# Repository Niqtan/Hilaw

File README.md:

# Hilaw (3D Printed Instant Camera)

## Project Aims

Hilaw, in english, Raw, is a hybrid analog & digital camera used for taking personal pictures in order to preserve memories. 

Before snapping a picture, a sample image will pop up in the TFT display, having a preview unlike traditional polaroid cameras. Then, using an Arducam module as the camera sensor, it is able to capture images with of high quality.

Afterwards, logic is sent to the thermal printer to print that picture instantly. In the long term, using a thermal printer with sticker paper (I want to be able to stick my memories), will be very cost-effective than traditional film paper, albeit only white and black colors will be in the picture when printing.

Image 1. Concept of the project
Courtesy of [TrendHunter](https://www.trendhunter.com/trends/thermal-print-camera)

## Power Management PCB

Image 2. Top view of PCB

Image 3. Bottom view of PCB

## Layout & Schematic

Image 4. PCB Layout & Connections 

Image 5. Power Schematic of the PCB

P.S. The PCB was mainly used for creating a power management module just for this. The rest are pretty much built-in modules to buy.

## CAD

Image 6. Exploded View of the CAD

Image 7. Side View of the CAD

Image 8. Top view of the CAD

Image 9. Bottom View of the CAD

## 3D Printing
In terms of 3D Printing this project, I will print this in Resin since some of these are curved (also the lens cutout is circular). You may print this in Resin with the following parameters:

Layer height: 0.05mm

Orientation: 30-45 degrees

thats pretty much it 

## BOM
[View the bom](BOM.csv)

## Firmware
Have not yet started on the firmware. I am going to choose the Arduino IDE in order to program the ESP32-WROOM-32 since it is much more convenient for prototyping.

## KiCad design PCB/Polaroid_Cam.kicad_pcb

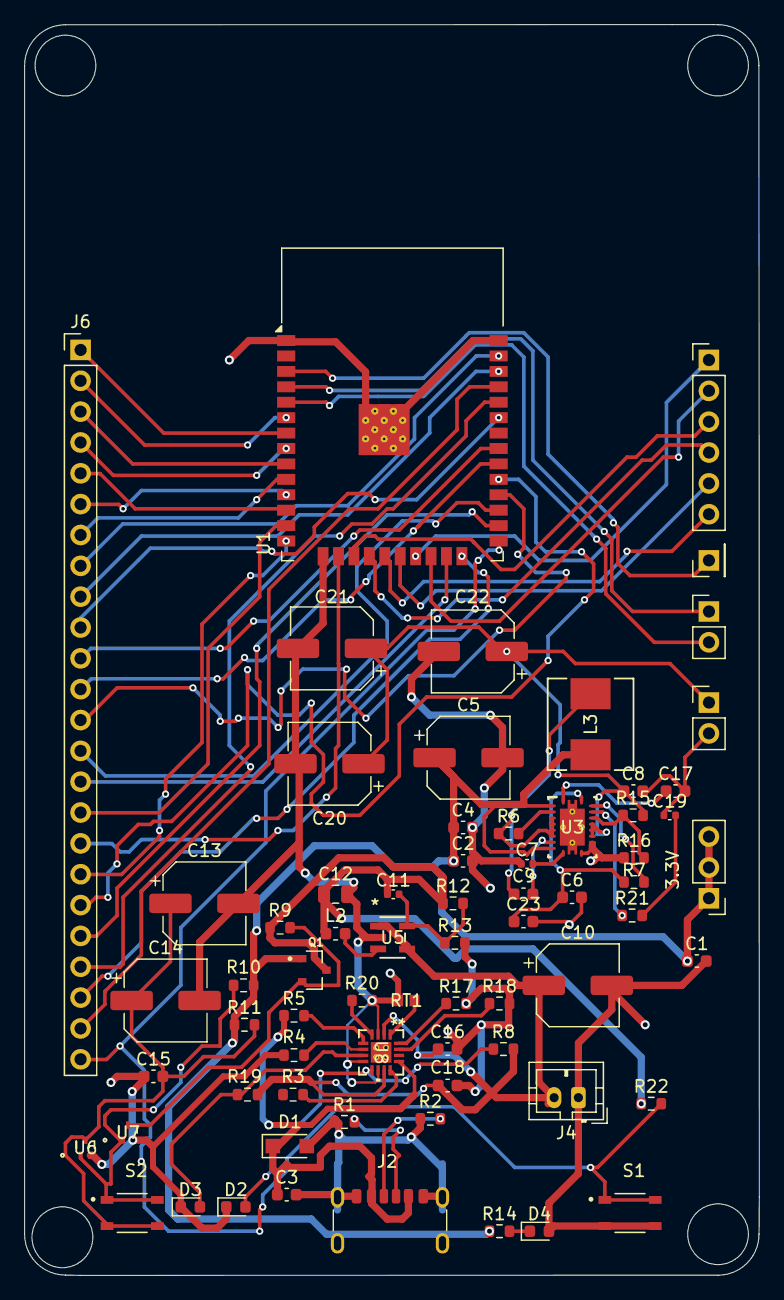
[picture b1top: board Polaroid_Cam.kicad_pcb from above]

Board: 2 copper layers, 60.5 x 103.0 mm, 69 parts (0 on the bottom side), 66 nets.

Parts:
C1, C2, C3, C4, C6, C8, C17: 1µ; C_0603_1608Metric
C5, C10, C13, C14, C20, C21, C22: 22µ; CP_Elec_6.3x5.4
C7: 47n; C_0402_1005Metric
C9, C23: 0.1µ; C_0603_1608Metric
C11: 4.1p; C_0402_1005Metric
C12: 10µ; C_0805_2012Metric
C15, C16, C18: 4.7μ; C_0603_1608Metric
C19: 87p; C_0402_1005Metric
D1: PTVS17VS1UR,115; Nexperia_CFP3_SOD-123W
D2, D3, D4: XL-1608PGC-06; LED_0603_1608Metric
J2: TYPE-C 6P LCH10.0; USB_C_Receptacle_GCT_USB4125-xx-x-0190_6P_TopMnt_Horizontal
J4: USE-702528-500PCBJST; JST_PH_B2B-PH-K_1x02_P2.00mm_Vertical
J5, J9: Conn_01x02_Pin; PinHeader_1x02_P2.54mm_Vertical
J6: Conn_01x24_Pin; PinHeader_1x24_P2.54mm_Vertical
J7: Conn_01x03_Pin; PinHeader_1x03_P2.54mm_Vertical
J8: Conn_01x06_Pin; PinHeader_1x06_P2.54mm_Vertical
J10: Conn_01x01_Pin; PinHeader_1x01_P2.54mm_Vertical
L2: 2.2µ; L_0603_1608Metric
L3: 2.2µ; IND_FXL0630_CMT
Q1: 2N7002BK, 215; TRANS_PMV130ENEAR
R1, R2: 56K; R_0603_1608Metric
R3, R8, R17, R19: 1k; R_0603_1608Metric
R4, R5, R18, R20, R22: 10k; R_0603_1608Metric
R6: 310k; R_0603_1608Metric
R7: 330K; R_0603_1608Metric
R9, R10: 10K; R_0603_1608Metric
R11: 700K; R_0603_1608Metric
R12: 240k; R_0603_1608Metric
R13: 53.6k; R_0603_1608Metric
R14: 100k; R_0603_1608Metric
R15: 30k; R_0603_1608Metric
R16: 4k7; R_0603_1608Metric
R21: 910k; R_0603_1608Metric
RT1: NCU18XH103F6SRB; TRES_NCU18XH103F6SRB_MUR
S1, S2: SKRPABE010; SW_SKRPABE010
U1: ESP32-WROOM-32
U3: TPS61088RHLR; RHL0020A
U5: RT8059GJ5; TSOT-23-5_RIT
U6, U7: MMBT2222AM3T5G; SOT-723_0P85X1P25_ONS-M
U8: BQ24075RGTR; RGT16_1P7X1P7

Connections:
+3.3V: C1.1, C2.1, C4.1, C5.1, C11.1, C12.1, J7.1, J7.2, J7.3, L2.2, L3.1, Q1.1 (S), Q1.3 (D), R9.1, R10.1, R11.1, R12.1, R14.1, R22.1, U3.2 (EN), U3.9 (VIN)
+3.7V: C10.1, C16.1, C18.1, J4.2, R8.2, R19.1, U5.1 (EN), U5.4 (VIN), U8.2 (BAT), U8.11 (OUT)
/Power Sheet/VBUS: C3.1, D1.1 (K), J2.A9 (VBUS), J2.B9 (VBUS), R5.1, U8.13 (IN)
AGround: C6.2, C23.2
GND: C1.2, C2.2, C3.2, C4.2, C5.2, C7.1, C8.2, C10.2, C12.2, C13.2, C14.2, C15.1, C16.2, C17.2, C18.2, C19.1, C20.2, C21.2, C22.2, D1.2 (A), D2.1 (K), D3.1 (K), D4.2 (A), J2.A12 (GND), J2.B12 (GND), J2.S1 (SHIELD), J4.1, J5.2, R1.1, R2.1, R3.2, R4.2, R13.2, R16.1, R17.2, R18.2, R20.2, RT1.1, S1.3, S1.4, U1.1 (GND), U1.15 (GND), U1.38 (GND), U1.39 (GND), U3.11 (NC), U3.12 (NC), U3.13 (MODE), U3.21 (PGND), U5.2 (GND), U6.2 (EMITTER), U7.2 (EMITTER), U8.3 (BAT), U8.8 (VSS), U8.10 (OUT), U8.17 (EPAD)
unnamed: C9.2, L3.2, R6.1, U3.4 (SW), U3.5 (SW), U3.6 (SW), U3.7 (SW)
unnamed: C19.2, R21.2
unnamed: D2.2 (A), R8.1, U8.9 (*CHG)
unnamed: D3.2 (A), R19.2, U8.7 (*PGOOD)
unnamed: D4.1 (K), R14.2
unnamed: J2.A5 (CC1), R2.2
unnamed: J2.B5 (CC2), R1.2
unnamed: C8.1, C20.1, C21.1, C22.1, J5.1, R15.2, U3.14 (VOUT), U3.15 (VOUT), U3.16 (VOUT)
unnamed: J6.1, U1.7 (IO35)
unnamed: J6.2, U1.6 (IO34)
unnamed: J6.3, U1.9 (IO33)
unnamed: J6.4, U1.8 (IO32)
unnamed: J6.5, U1.12 (IO27)
unnamed: J6.6, U1.11 (IO26)
unnamed: J6.7, U1.10 (IO25)
unnamed: J6.8, U1.37 (IO23)
unnamed: J6.9, U1.36 (IO22)
unnamed: J6.10, U1.33 (IO21)
unnamed: J6.11, U1.31 (IO19)
unnamed: J6.12, U1.30 (IO18)
unnamed: J6.13, U1.28 (IO17)
unnamed: J6.14, U1.27 (IO16)
unnamed: J6.15, U1.23 (IO15)
unnamed: J6.16, U1.13 (IO14)
unnamed: J6.17, U1.16 (IO13)
unnamed: J6.18, U1.14 (IO12)
unnamed: J6.19, U1.29 (IO5)
unnamed: J6.20, U1.26 (IO4)
unnamed: J6.21, U1.34 (RXD0/IO3)
unnamed: J6.22, U1.24 (IO2)
unnamed: J6.23, U1.35 (TXD0/IO1)
unnamed: J6.24, R22.2, S1.1, S1.2, U1.25 (IO0)
unnamed: J8.1, U1.21 (SDO/SD0)
unnamed: J8.2, U1.22 (SDI/SD1)
unnamed: J8.3, U1.17 (SHD/SD2)
unnamed: J8.4, U1.18 (SWP/SD3)
unnamed: J8.5, U1.20 (SCK/CLK)
unnamed: J8.6, U1.19 (SCS/CMD)
unnamed: J9.1, U1.4 (SENSOR_VP)
unnamed: J9.2, U1.5 (SENSOR_VN)
unnamed: J10.1, U1.3 (EN)
unnamed: Q1.2 (G), R9.2, U7.3 (COLLECTOR)
unnamed: C6.1, C23.1, R7.2, U3.20 (AGND)
unnamed: C9.1, U3.8 (BOOT)
unnamed: R21.1, U3.18 (COMP)
unnamed: R15.1, R16.2, U3.17 (FB)
unnamed: R6.2, U3.3 (FSW)
unnamed: R7.1, U3.19 (ILIM)
unnamed: C7.2, U3.10 (SS)
unnamed: C17.1, U3.1 (VCC)
unnamed: C11.2, R12.2, R13.1, U5.5 (FB)
unnamed: L2.1, U5.3 (LLX)
unnamed: R10.2, S2.1, S2.2, U6.1 (BASE), U7.1 (BASE)
unnamed: C13.1, C14.1, C15.2, R11.2, S2.3, S2.4, U6.3 (COLLECTOR)
unnamed: R20.1, U8.4 (*CE)
unnamed: R4.1, U8.6 (EN1)
unnamed: R5.2, U8.5 (EN2)
unnamed: R3.1, U8.12 (ILIM)
unnamed: R17.1, U8.16 (ISET)
unnamed: R18.1, U8.15 (SYSOFF)
unnamed: RT1.2, U8.1 (TS)

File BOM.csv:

Comment,Designator,Footprint,LCSC Part #,Total (USD)
1µ Unpolarized capacitor,"C1,C2,C3,C4,C6,C8,C17",C_0603_1608Metric,C1592,IN PCBA
22µ Polarized capacitor,"C5,C10,C13,C14,C20,C21,C22",CP_Elec_6.3x5.4,C7469954,IN PCBA
47n Unpolarized capacitor,C7,C_0402_1005Metric,C1525,IN PCBA
0.1µ Unpolarized capacitor,"C9,C23",C_0603_1608Metric,C1590,IN PCBA
4.1p Unpolarized capacitor,C11,C_0402_1005Metric,C1525,IN PCBA
10µ Unpolarized capacitor,C12,C_0805_2012Metric,C1713,IN PCBA
4.7μ Unpolarized capacitor,"C15,C16,C18",C_0603_1608Metric,C1705,IN PCBA
87p Unpolarized capacitor,C19,C_0402_1005Metric,C1525,IN PCBA
"PTVS17VS1UR,115 Zener diode",D1,Nexperia_CFP3_SOD-123W,C396100,IN PCBA
XL-1608PGC-06 Light emitting diode,"D2,D3,D4",LED_0603_1608Metric,C7371905,IN PCBA
USB_C_Receptacle_GCT_USB4125-xx-x-0190_6P_TopMnt_Horizontal,J2,TYPE-C 6P LCH10.0 USB Power-Only 6P Type-C Receptacle connector,C5187470,IN PCBA
"USE-702528-500PCBJST Generic connector, single row, 01x02, script generated",J4,JST_PH_B2B-PH-K_1x02_P2.00mm_Vertical,C5251182,IN PCBA
"Conn_01x24_Pin Generic connector, single row, 01x24, script generated",J6,PinHeader_1x24_P2.54mm_Vertical,C7430380,IN PCBA
"Conn_01x03_Pin Generic connector, single row, 01x03, script generated",J7,PinHeader_1x03_P2.54mm_Vertical,C49257,IN PCBA
"Conn_01x06_Pin Generic connector, single row, 01x06, script generated",J8,PinHeader_1x06_P2.54mm_Vertical,C37208,IN PCBA
"Conn_01x01_Pin Generic connector, single row, 01x01, script generated",J10,PinHeader_1x01_P2.54mm_Vertical,C81276,IN PCBA
2.2µ Inductor,L2,L_0603_1608Metric,C1033,IN PCBA
2.2µ Inductor,L3,IND_FXL0630_CMT,C167211,IN PCBA
"2N7002BK, 215 0.2A Id, 200V Vds, N-Channel MOSFET, 2.6V Logic Level, TO-92",Q1,TRANS_PMV130ENEAR,C458143,IN PCBA
56K Resistora,"R1,R2",R_0603_1608Metric,C23206,IN PCBA
1k Resistor,"R3,R8,R17,R19",R_0603_1608Metric,C11702,IN PCBA
10k Resistor,"R4,R5,R18,R20,R22",R_0603_1608Metric,C25804,IN PCBA
310k Resistor,R6,R_0603_1608Metric,C23137,IN PCBA
330K Resistor,R7,R_0603_1608Metric,C23137,IN PCBA
10K Resistor,"R9,R10",R_0603_1608Metric,C25804,IN PCBA
700K Resistor,R11,R_0603_1608Metric,"C25606
",IN PCBA
240k Resistor,R12,R_0603_1608Metric,C4197,IN PCBA
53.6k Resistor,R13,R_0603_1608Metric,C23074,IN PCBA
100k Resistor,R14,R_0603_1608Metric,C25803,IN PCBA
30k Resistor,R15,R_0603_1608Metric,C18681,IN PCBA
4k7 Resistor,R16,R_0603_1608Metric,C100444,IN PCBA
910k Resistor,R21,R_0603_1608Metric,C23263,IN PCBA
NCU18XH103F6SRB,RT1,TRES_NCU18XH103F6SRB_MUR,C162670,IN PCBA
SKRPABE010,"S1,S2",SW_SKRPABE010,C115360,IN PCBA
"ESP32-WROOM-32 RF Module, ESP32-D0WDQ6 SoC, Wi-Fi 802.11b/g/n, Bluetooth, BLE, 32-bit, 2.7-3.6V, onboard antenna, SMD",U1,ESP32-WROOM-32,"C82899",IN PCBA
TPS61088RHLR,U3,RHL0020A,C87357,IN PCBA
RT8059GJ5,U5,TSOT-23-5_RIT,C20542,IN PCBA
MMBT2222AM3T5G,"U6,U7",SOT-723_0P85X1P25_ONS-M,C896289,IN PCBA
BQ24075RGTR,U8,RGT16_1P7X1P7,"
C15464",IN PCBA
NOT IN PCB,,,,IN PCBA
ARDUCAM (B0401),N/A,N/A,N/A,$53.66
GOOJPRT QR204 Thermal Printer,N/A,N/A,N/A,$20.18
TFT_320x240 ( provided) ,N/A,N/A,N/A,$0
,,,,
Shipping & Etc,,,,
Aliexpress Thermal Printer ,,,,$16.87
PCBA Assembly,,,,$102.55
PCB & PCBA Shipping,,,,$11.72
,,,,$204.98

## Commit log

2025-07-08 initialize
2025-07-24 did some journalling
2025-07-26 readme
2025-07-26 journal and BOM
2025-07-26 fixed smth in readme
2025-07-26 polished stuff
2025-07-26 updated BOM
2025-07-27 update files
2025-07-31 updated journal
2025-08-10 updated journal and firmware
